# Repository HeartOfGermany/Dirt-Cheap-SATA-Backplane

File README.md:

# Dirt-Cheap-SATA-Backplane

## Front side (left/first) and back side

<picture>
  
</picture>
<picture>
  
</picture>

This repo is intended to share plans for a super cheap DIY backplane. It is using KiCad and it fits the 100x100mm default of JLCPCB

Example: 100x100mm PCB x10pcs costs 15€ delivered to europe as the time of writing this. So 1 Backplane PCB costs just 1.50€ plus components. It uses 1.6mm 2 layer FR4.

## Features:
- LED Indicators
  - Activity LED (Bi-Color support!)
  - HDD Detect LED
  - 12V Power OK
  - 5V Power OK
  - 3.3V Power OK
  - 5V Power generator activated
  - 3.3V Power generator activated
- SATA or Floppy power input (or just solder your custom cable)
  - 12V only input (generate 5V and 3.3V automatically)
  - 12V+5V input (generate 3.3V automatically)
- Optional components
  - Do not need certain Indicators? Than leave them out
  - Do not need 5V or 3.3V generation? Than just do not solder in the converters
  - Just want to solder THT and NO SMD? Can do just that (But Activity LED requires 2 SOT23 transistors - but easier to solder than TO-92!
  - Just want to solder SMD? Also fine!
  - LED indicators to back side or front side? Do as you wish
  - Do not want to solder tons of decoupling? Just leave it out. It is optional and I only use the caps in the converter section of the schematic 

## How to use?
Steps:
1. Develop the board (JLCPCB worked fine for me)
2. Meanwhile order the Components, check the Schematic for purchasing links (no affiliate!)
3. Solder the components as you like
4. Test with an old HDD first!
5. Design some enclosure or cage, where you can screw the PCB onto the backside to slide it in and out again. After all... it is a Hot-Swap SATA Backplane. I used some wooden boards from an old drawer with some cut slots and a laser to get some ventilation slots. Than I used thin ply wood to mount the HDDs on (3mm max. recommended). These ply wood plates can slide in and out on the slotted boards, which form the surrounding. The uplink connectors are on the outside of the board. I will see if I will attach a reference image... Use your brain, it's not hard to build stuff!
6. How to nail alignment? The PCB has some mounting holes. Get yourself some flat standoffs and screw them in. Use some Alc to clean the backplate and the standoffs for adheasion. Now plug an upper and lower HDD in at least, to get the proper alignment. Use a dab of epoxy and just lay it on the backplate. The standoffs will glue in over the course of 24h (some gentle heat like 40-50°C speeds up a lot!) and you can than mount and unmount this as often by just unscrewing the screws (remember: after on comes off, so do not overtorque!). I recommend adding another layer to reinforce the joint and maybe even roughen the standoffs for better adheason, aswell as adding filler like quarz sand to the epoxy, to get a dang resilient, thick bond.

## Attention:
**DO**
- Use Flux. Tons of flux. If you are too cheap, use at least some Rosin intended for inhalation - it comes in 100g bags for just 2-3 bucks and is more efficient than those tiny containers with like 10g rosin.
- How to clean the flux residue easily? Use denatured Alc or Isopropyl to soak and than clean the board. You can also soak the board by wrapping in toilet paper and soaking it in Alc and leav it over night in a bag. Next day use tooth brush and carefully mobilize the rest of residues. Use some more to wash the rest away and your board will look like from factory
- Use enough heat! I make a lot of use of ground planes. Heat joints as fast as possible and go away to not damage components
- SATA connectors are hard to find on many proper stores, I got mine from Aliexpress - just double check the images to the PCB before ordering. The PCB allows some variation (Holes larger than needed). In theory you could also solder SMD equivalents in, if you can find some
- The Schematic contains a section "Parts List". A lot is from LCSC from China. It is like a dirt cheap Mouser/Digikey alternative, but of amazing quality. If you are cheap but want to ensure original components only, go there for your parts!
- Consider a Bismuth solder and some Amtech 559, if you are new to soldering. Requiring like 50K less temperature helps a LOT. It gives a ton of time to work on joints and constantly reflow, without overheating components (Especially ceramic caps are sensitive to re-heating a lot - could short)

**DON'T**
- Do not enable 3.3V or 5V generation, if your power input already supplies it! Check with the Voltage OK LEDs first! Otherwise the tiny buck converters try to provide 5V and 3.3V to your PC, which they cannot handle and they WILL overheat, potentially with permanent damage to the PCB.
- Do not use other thicknesses or materials than 1.6mm FR4!!! These could mess with the differential pair signalling, as the ground plane distance is very important to keep proper impedance
- Do NOT forget to use tons of flux. The PCB is easy to solder, if you use a decent cheap 60€/$ solder station with hot air, if Flux and Solder are good. Leaded solder helps a lot (though not healthy), or bismuth solder. Bismuth solder is a lot more brittle. Ensure, that the fillets form perfectly or rework them before use.

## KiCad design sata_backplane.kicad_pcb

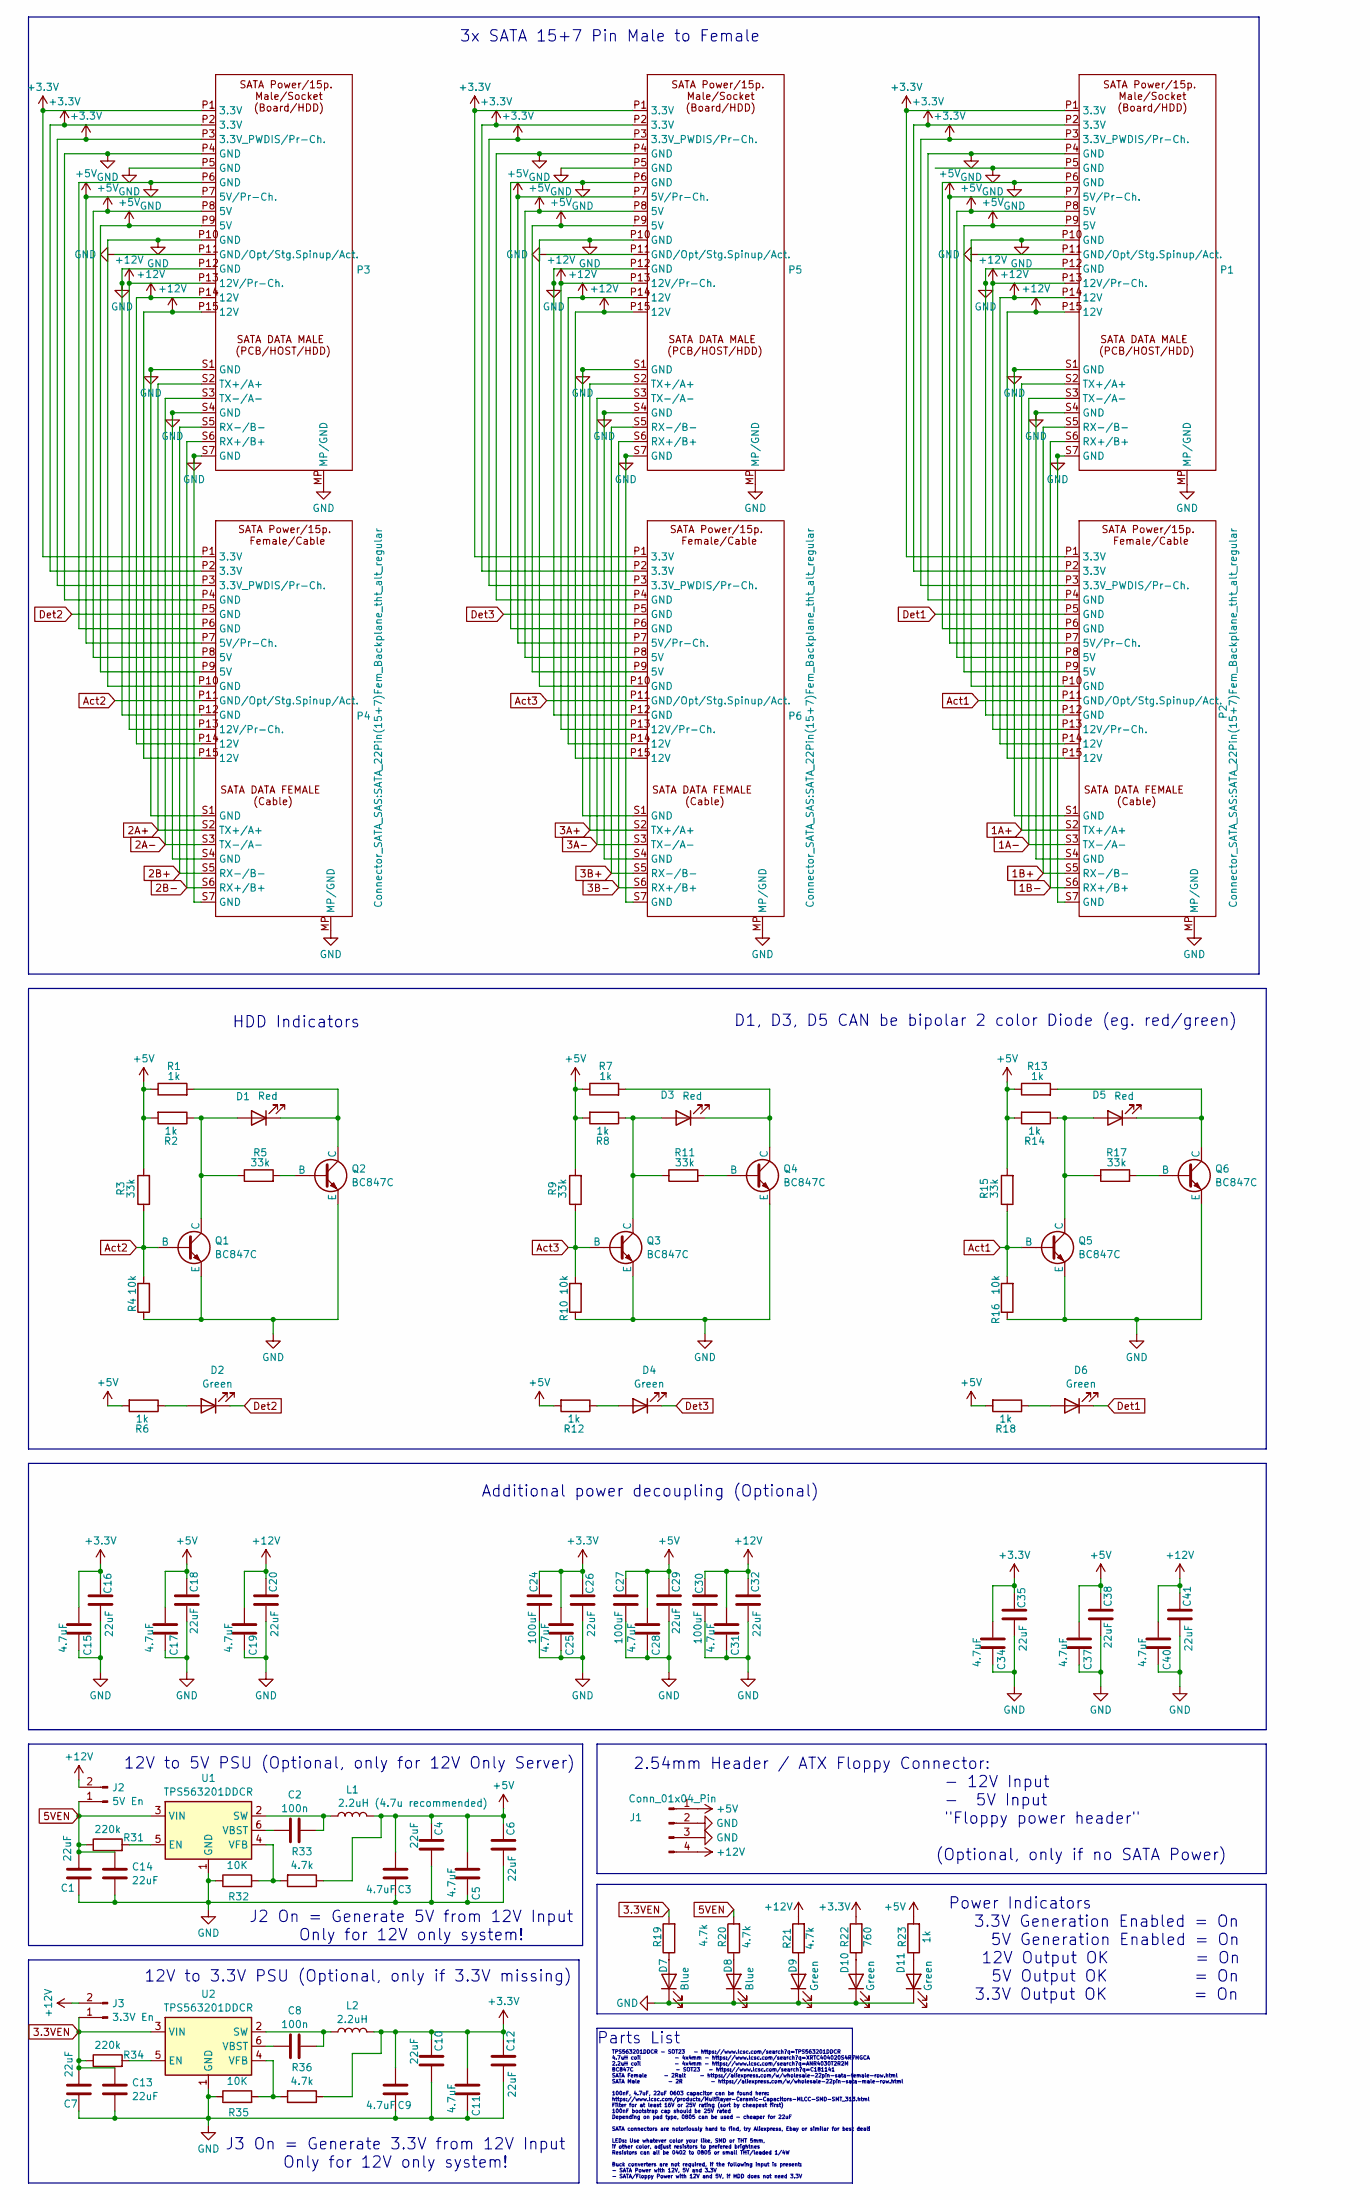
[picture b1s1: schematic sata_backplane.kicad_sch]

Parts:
C1, C7, C13, C14: 22uF; C_0402_1005Metric_Pad0.74x0.62mm_HandSolder
C2, C8: 100n; C_0402_1005Metric_Pad0.74x0.62mm_HandSolder
C3, C5, C9, C11, C15, C17, C19, C25, C28, C31, C34, C37, C40: 4.7uF; C_0402_1005Metric_Pad0.74x0.62mm_HandSolder
C4, C6, C10, C12, C16, C18, C20, C26, C29, C32, C35, C38, C41: 22uF; C_0805_2012Metric_Pad1.18x1.45mm_HandSolder
C24, C27, C30: 100uF; CP_Radial_D8.0mm_P5.00mm
D1, D3, D5: Red; Diode_SMD_THT_5mm_combi
D2, D4, D6, D9, D10, D11: Green; Diode_SMD_THT_5mm_combi
D7, D8: Blue; Diode_SMD_THT_5mm_combi
J1: Conn_01x04_Pin; PinHeader_1x04_P2.54mm_Vertical
J2: 5V En; PinHeader_1x02_P2.54mm_Vertical
J3: 3.3V En; PinHeader_1x02_P2.54mm_Vertical
L1: 2.2uH (4.7u recommended); L_1210_3225Metric_Pad1.42x2.65mm_HandSolder
L2: 2.2uH; L_1210_3225Metric_Pad1.42x2.65mm_HandSolder
P1, P3, P5: SATA_22Pin(15+7)Fem_Backplane_tht_lin
P2, P4, P6: SATA_22Pin(15+7)Fem_Backplane_tht_alt_regular
Q1, Q2, Q3, Q4, Q5, Q6: BC847C; SOT-23-3-Correct
R1, R2, R6, R7, R8, R12, R13, R14, R18, R23: 1k; R_Axial_L3.6_D1.6_P5.08_0805SMD_Combi
R3, R5, R9, R11, R15, R17: 33k; R_Axial_L3.6_D1.6_P5.08_0805SMD_Combi
R4, R10, R16: 10k; R_Axial_L3.6_D1.6_P5.08_0805SMD_Combi
R19, R20, R21: 4.7k; R_Axial_L3.6_D1.6_P5.08_0805SMD_Combi
R22: 760; R_Axial_L3.6_D1.6_P5.08_0805SMD_Combi
R31, R34: 220k; R_0402_1005Metric_Pad0.72x0.64mm_HandSolder
R32, R35: 10K; R_0402_1005Metric_Pad0.72x0.64mm_HandSolder
R33, R36: 4.7k; R_0402_1005Metric_Pad0.72x0.64mm_HandSolder
U1, U2: TPS563201DDCR; SOT-23-6

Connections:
1A+: P1.S2 (TX+/A+), P2.S2 (TX+/A+)
1A-: P1.S3 (TX-/A-), P2.S3 (TX-/A-)
1B+: P1.S5 (RX-/B-), P2.S5 (RX-/B-)
1B-: P1.S6 (RX+/B+), P2.S6 (RX+/B+)
2A+: P3.S2 (TX+/A+), P4.S2 (TX+/A+)
2A-: P3.S3 (TX-/A-), P4.S3 (TX-/A-)
2B+: P3.S5 (RX-/B-), P4.S5 (RX-/B-)
2B-: P3.S6 (RX+/B+), P4.S6 (RX+/B+)
3.3VEN: C7.2, C13.2, J3.1, R19.2, R34.1, U2.3 (VIN)
3A+: P5.S2 (TX+/A+), P6.S2 (TX+/A+)
3A-: P5.S3 (TX-/A-), P6.S3 (TX-/A-)
3B+: P5.S5 (RX-/B-), P6.S5 (RX-/B-)
3B-: P5.S6 (RX+/B+), P6.S6 (RX+/B+)
5VEN: C1.2, C14.2, J2.1, R20.2, R31.1, U1.3 (VIN)
+3.3V: C9.2, C10.2, C11.2, C12.2, C15.2, C16.2, C24.2, C25.2, C26.2, C34.2, C35.2, L2.2, P1.P1 (3.3V), P1.P2 (3.3V), P1.P3 (3.3V_PWDIS/Pr-Ch.), P2.P1 (3.3V), P2.P2 (3.3V), P2.P3 (3.3V_PWDIS/Pr-Ch.), P3.P1 (3.3V), P3.P2 (3.3V), P3.P3 (3.3V_PWDIS/Pr-Ch.), P4.P1 (3.3V), P4.P2 (3.3V), P4.P3 (3.3V_PWDIS/Pr-Ch.), P5.P1 (3.3V), P5.P2 (3.3V), P5.P3 (3.3V_PWDIS/Pr-Ch.), P6.P1 (3.3V), P6.P2 (3.3V), P6.P3 (3.3V_PWDIS/Pr-Ch.), R22.2, R36.1
+5V: C3.2, C4.2, C5.2, C6.2, C17.2, C18.2, C27.2, C28.2, C29.2, C37.2, C38.2, J1.1, L1.2, P1.P7 (5V/Pr-Ch.), P1.P8 (5V), P1.P9 (5V), P2.P7 (5V/Pr-Ch.), P2.P8 (5V), P2.P9 (5V), P3.P7 (5V/Pr-Ch.), P3.P8 (5V), P3.P9 (5V), P4.P7 (5V/Pr-Ch.), P4.P8 (5V), P4.P9 (5V), P5.P7 (5V/Pr-Ch.), P5.P8 (5V), P5.P9 (5V), P6.P7 (5V/Pr-Ch.), P6.P8 (5V), P6.P9 (5V), R1.1, R2.2, R3.2, R6.2, R7.1, R8.2, R9.2, R12.2, R13.1, R14.2, R15.2, R18.2, R23.2, R33.1
+12V: C19.2, C20.2, C30.2, C31.2, C32.2, C40.2, C41.2, J1.4, J2.2, J3.2, P1.P13 (12V/Pr-Ch.), P1.P14 (12V), P1.P15 (12V), P2.P13 (12V/Pr-Ch.), P2.P14 (12V), P2.P15 (12V), P3.P13 (12V/Pr-Ch.), P3.P14 (12V), P3.P15 (12V), P4.P13 (12V/Pr-Ch.), P4.P14 (12V), P4.P15 (12V), P5.P13 (12V/Pr-Ch.), P5.P14 (12V), P5.P15 (12V), P6.P13 (12V/Pr-Ch.), P6.P14 (12V), P6.P15 (12V), R21.2
Act1: P2.P11 (GND/Opt/Stg.Spinup/Act.), Q5.2 (B), R15.1, R16.2
Act2: P4.P11 (GND/Opt/Stg.Spinup/Act.), Q1.2 (B), R3.1, R4.2
Act3: P6.P11 (GND/Opt/Stg.Spinup/Act.), Q3.2 (B), R9.1, R10.2
Det1: D6.1 (K), P2.P5 (GND)
Det2: D2.1 (K), P4.P5 (GND)
Det3: D4.1 (K), P6.P5 (GND)
GND: C1.1, C3.1, C4.1, C5.1, C6.1, C7.1, C9.1, C10.1, C11.1, C12.1, C13.1, C14.1, C15.1, C16.1, C17.1, C18.1, C19.1, C20.1, C24.1, C25.1, C26.1, C27.1, C28.1, C29.1, C30.1, C31.1, C32.1, C34.1, C35.1, C37.1, C38.1, C40.1, C41.1, D7.1 (K), D8.1 (K), D9.1 (K), D10.1 (K), D11.1 (K), J1.2, J1.3, P1.MP (MP/GND), P1.P4 (GND), P1.P5 (GND), P1.P6 (GND), P1.P10 (GND), P1.P11 (GND/Opt/Stg.Spinup/Act.), P1.P12 (GND), P1.S1 (GND), P1.S4 (GND), P1.S7 (GND), P2.MP (MP/GND), P2.P4 (GND), P2.P6 (GND), P2.P10 (GND), P2.P12 (GND), P2.S1 (GND), P2.S4 (GND), P2.S7 (GND), P3.MP (MP/GND), P3.P4 (GND), P3.P5 (GND), P3.P6 (GND), P3.P10 (GND), P3.P11 (GND/Opt/Stg.Spinup/Act.), P3.P12 (GND), P3.S1 (GND), P3.S4 (GND), P3.S7 (GND), P4.MP (MP/GND), P4.P4 (GND), P4.P6 (GND), P4.P10 (GND), P4.P12 (GND), P4.S1 (GND), P4.S4 (GND), P4.S7 (GND), P5.MP (MP/GND), P5.P4 (GND), P5.P5 (GND), P5.P6 (GND), P5.P10 (GND), P5.P11 (GND/Opt/Stg.Spinup/Act.), P5.P12 (GND), P5.S1 (GND), P5.S4 (GND), P5.S7 (GND), P6.MP (MP/GND), P6.P4 (GND), P6.P6 (GND), P6.P10 (GND), P6.P12 (GND), P6.S1 (GND), P6.S4 (GND), P6.S7 (GND), Q1.3 (E), Q2.3 (E), Q3.3 (E), Q4.3 (E), Q5.3 (E), Q6.3 (E), R4.1, R10.1, R16.1, R32.1, R35.1, U1.1 (GND), U2.1 (GND)
unnamed: D1.2 (A), Q1.1 (C), R2.1, R5.1
unnamed: D1.1 (K), Q2.1 (C), R1.2
unnamed: D2.2 (A), R6.1
unnamed: D3.2 (A), Q3.1 (C), R8.1, R11.1
unnamed: D3.1 (K), Q4.1 (C), R7.2
unnamed: D4.2 (A), R12.1
unnamed: D5.2 (A), Q5.1 (C), R14.1, R17.1
unnamed: D5.1 (K), Q6.1 (C), R13.2
unnamed: D6.2 (A), R18.1
unnamed: D7.2 (A), R19.1
unnamed: D8.2 (A), R20.1
unnamed: D9.2 (A), R21.1
unnamed: D10.2 (A), R22.1
unnamed: D11.2 (A), R23.1
unnamed: Q2.2 (B), R5.2
unnamed: Q4.2 (B), R11.2
unnamed: Q6.2 (B), R17.2
unnamed: R31.2, U1.5 (EN)
unnamed: C2.1, L1.1, U1.2 (SW)
unnamed: C2.2, U1.6 (VBST)
unnamed: R32.2, R33.2, U1.4 (VFB)
unnamed: R34.2, U2.5 (EN)
unnamed: C8.1, L2.1, U2.2 (SW)
unnamed: C8.2, U2.6 (VBST)
unnamed: R35.2, R36.2, U2.4 (VFB)

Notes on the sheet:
J2 On = Generate 5V from 12V Input Only for 12V only system!
J3 On = Generate 3.3V from 12V Input Only for 12V only system!
12V to 5V PSU (Optional, only for 12V Only Server)
TPS563201DDCR - SOT23 - https://www.lcsc.com/search?q=TPS563201DDCR 4.7uH coil - 4x4mm - https://www.lcsc.com/search?q=XRTC404020S4R7MGCA 2.2uH coil - 4x4mm - https://www.lcsc.com/search?q=ANR4030T2R2M BC847C - SOT23 - https://www.lcsc.com/search?q=C181141 SATA Female - 2Ralt - https://aliexpress.c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
D1, D3, D5 CAN be bipolar 2 color Diode (eg. red/green)
HDD Indicators
Parts List
3x SATA 15+7 Pin Male to Female
12V to 3.3V PSU (Optional, only if 3.3V missing)
Power Indicators 3.3V Generation Enabled = On 5V Generation Enabled = On 12V Output OK = On 5V Output OK = On 3.3V Output OK = On
2.54mm Header / ATX Floppy Connector: - 12V Input - 5V Input "Floppy power header" (Optional, only if no SATA Power)
Additional power decoupling (Optional)

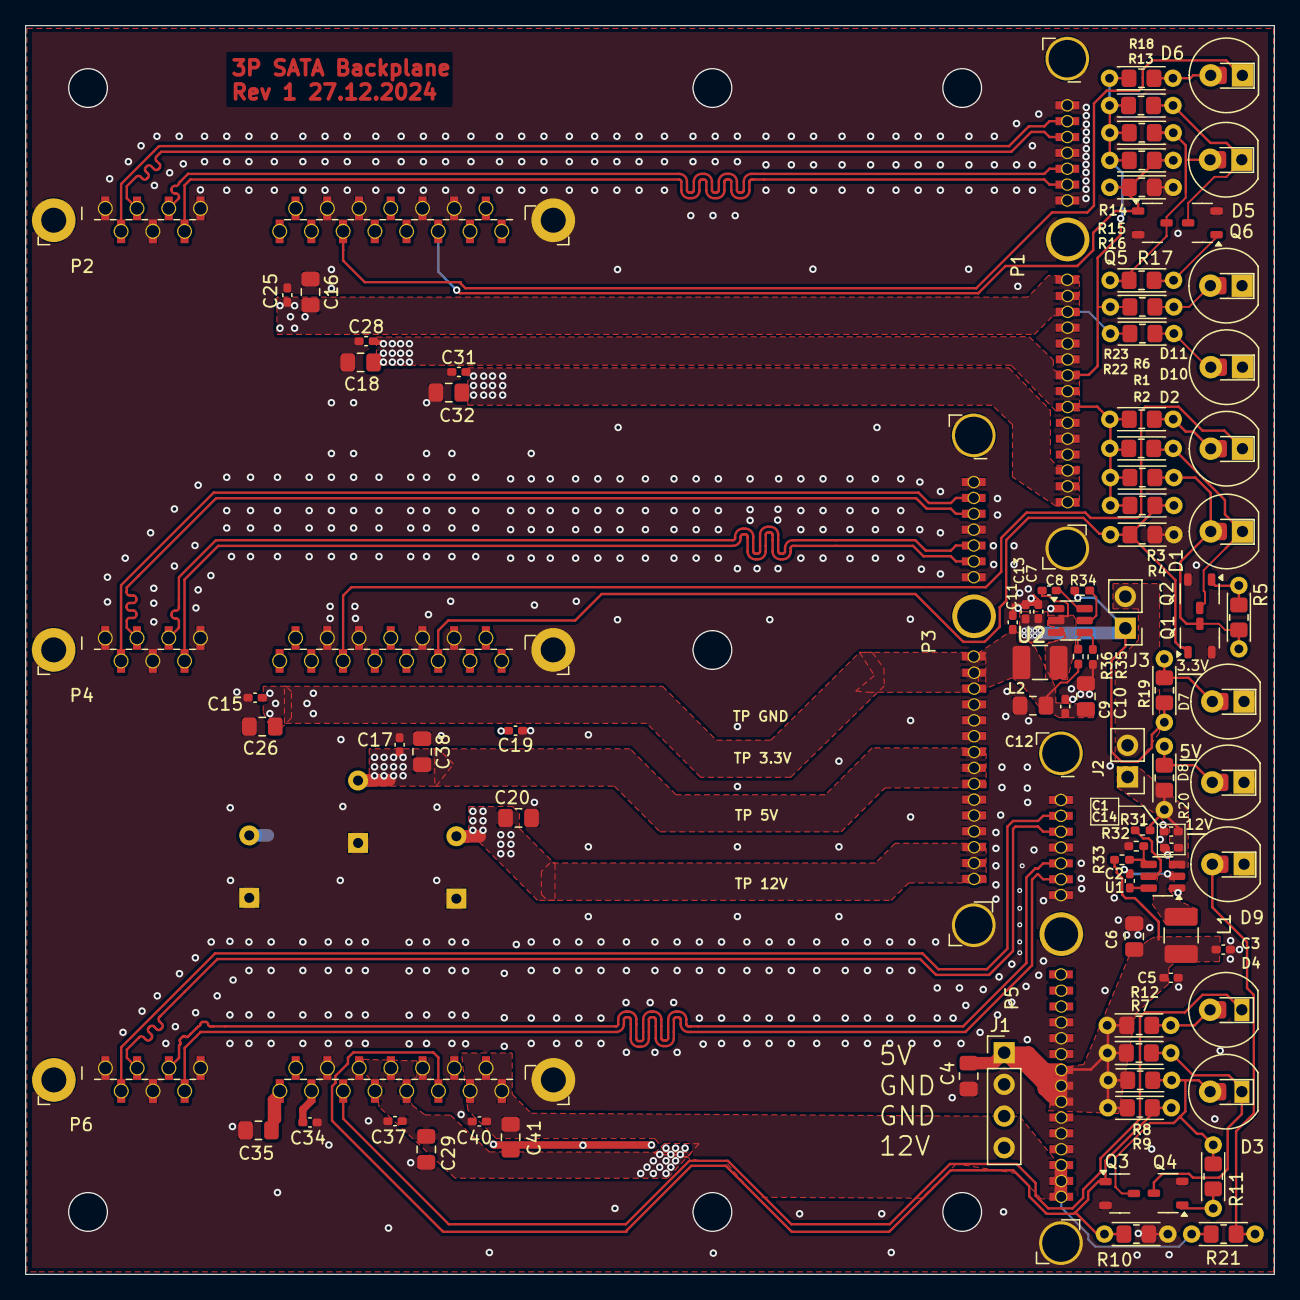
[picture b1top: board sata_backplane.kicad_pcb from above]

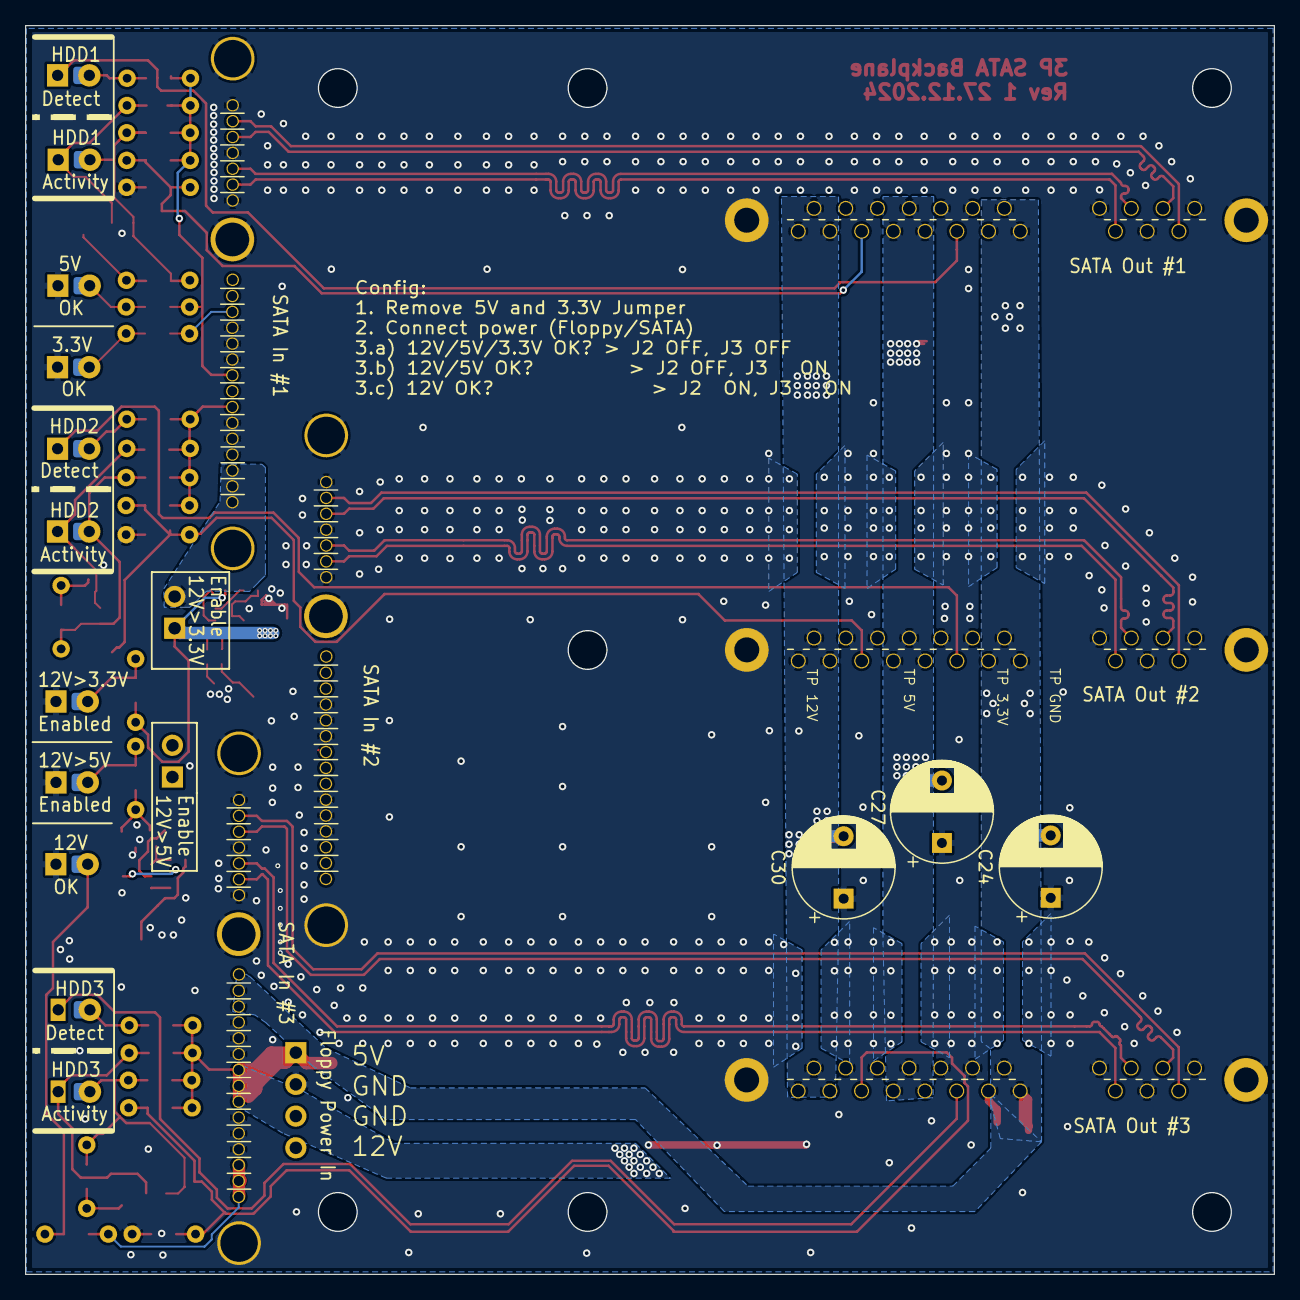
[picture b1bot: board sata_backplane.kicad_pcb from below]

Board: 2 copper layers, 100.0 x 100.0 mm, 94 parts (3 on the bottom side), 49 nets.

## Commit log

2024-12-29 Version 1
    + Front/Back side image
2024-12-30 Update README.md
    Added images
